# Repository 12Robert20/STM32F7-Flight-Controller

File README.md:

# 🚀 LayerByLayer Flight Controller v0.1.0

A high-performance, 4-layer custom Flight Controller designed in KiCad 8. Built around the powerful STM32F777 microcontroller, it features an advanced IMU, integrated OSD, and Blackbox logging capabilities, tailored for demanding FPV and autonomous flight applications.

---

## ✨ Key Features & Hardware Specifications

*   **Microcontroller:** `STM32F777VIT6` (ARM Cortex-M7, 216MHz, 2MB Flash, 512KB RAM)
*   **IMU (Gyro/Accel):** `LSM6DSV320XTR` (Connected via SPI6)
*   **OSD (On-Screen Display):** `MAX7456EUI+` (Analog Video Overlay, SPI4)
*   **Barometer:** `BMP280` (Altitude sensing, I2C1)
*   **Blackbox Flash:** `W25Q128JVS` (16MB/128Mbit SPI Flash for flight data logging, SPI3)
*   **USB Interface:** USB-C 2.0 with `USBLC6-2SC6` ESD protection diode.

---

## ⚡ Power Delivery Network (PDN)

To ensure clean video feeds and stable logic levels, the power delivery is split and filtered:
*   **Main 5V Buck Converter:** Direct LiPo input (VBAT) is stepped down by an `LMR51430Y` synchronous buck converter, providing a highly efficient 5V at up to 3A for the MCU, OSD, and external peripherals (VTX, Camera, GPS).
*   **Clean Video:** A dedicated LC filter is implemented before the VTX/Camera power rail to eliminate electrical noise generated by the ESCs and motors.
*   **3.3V Logic LDO:** An `AP2112K-3.3` linear regulator derives a clean 3.3V from the 5V rail to power the noise-sensitive STM32 MCU, IMU, Baro, and Flash memory.

---

## 🔌 Connectivity & Interfaces

| Interface | Bus / Pins | Description |
| :--- | :--- | :--- |
| **ESC / Motors** | `M1` - `M4` | 4x Motor Outputs (DShot600 compatible) |
| **Receiver (RX)** | `UART1` | CRSF Protocol (e.g., TBS Crossfire, ExpressLRS) |
| **GPS / Compass** | `UART2` + `I2C1` | GNSS Module connectivity |
| **Video TX (VTX)** | Video Out | 5V, GND, Video Signal (SpeedyBee TX800 VTX support) |
| **Camera** | Video In | 5V, GND, Video Signal (Analog Camera e.g., CADDXFPV) |
| **Debug** | `SWD` | SWCLK / SWDIO pads for ST-Link debugging |

---

## 🛠️ PCB Stackup (4-Layer)

To ensure signal integrity and controlled impedance for high-speed traces, a standard 4-layer stackup is utilized:
1.  **F.Cu (Top):** Signal & Components
2.  **In1.Cu (Inner 1):** Solid GND Plane
3.  **In2.Cu (Inner 2):** Split Power Planes (3.3V / 5V / VBAT)
4.  **B.Cu (Bottom):** Signal & Minor Components

---

## 🚧🚧🚧 📝 Firmware Compatibility (In Development) 🚧🚧🚧

This hardware is architected to be compatible with major open-source flight controller firmware. Custom target definition files are required to map the pins correctly.
*   **Betaflight** (Recommended for FPV)
*   **INAV** (Recommended for Autonomous Flight utilizing the onboard BMP280 and GNSS UART)

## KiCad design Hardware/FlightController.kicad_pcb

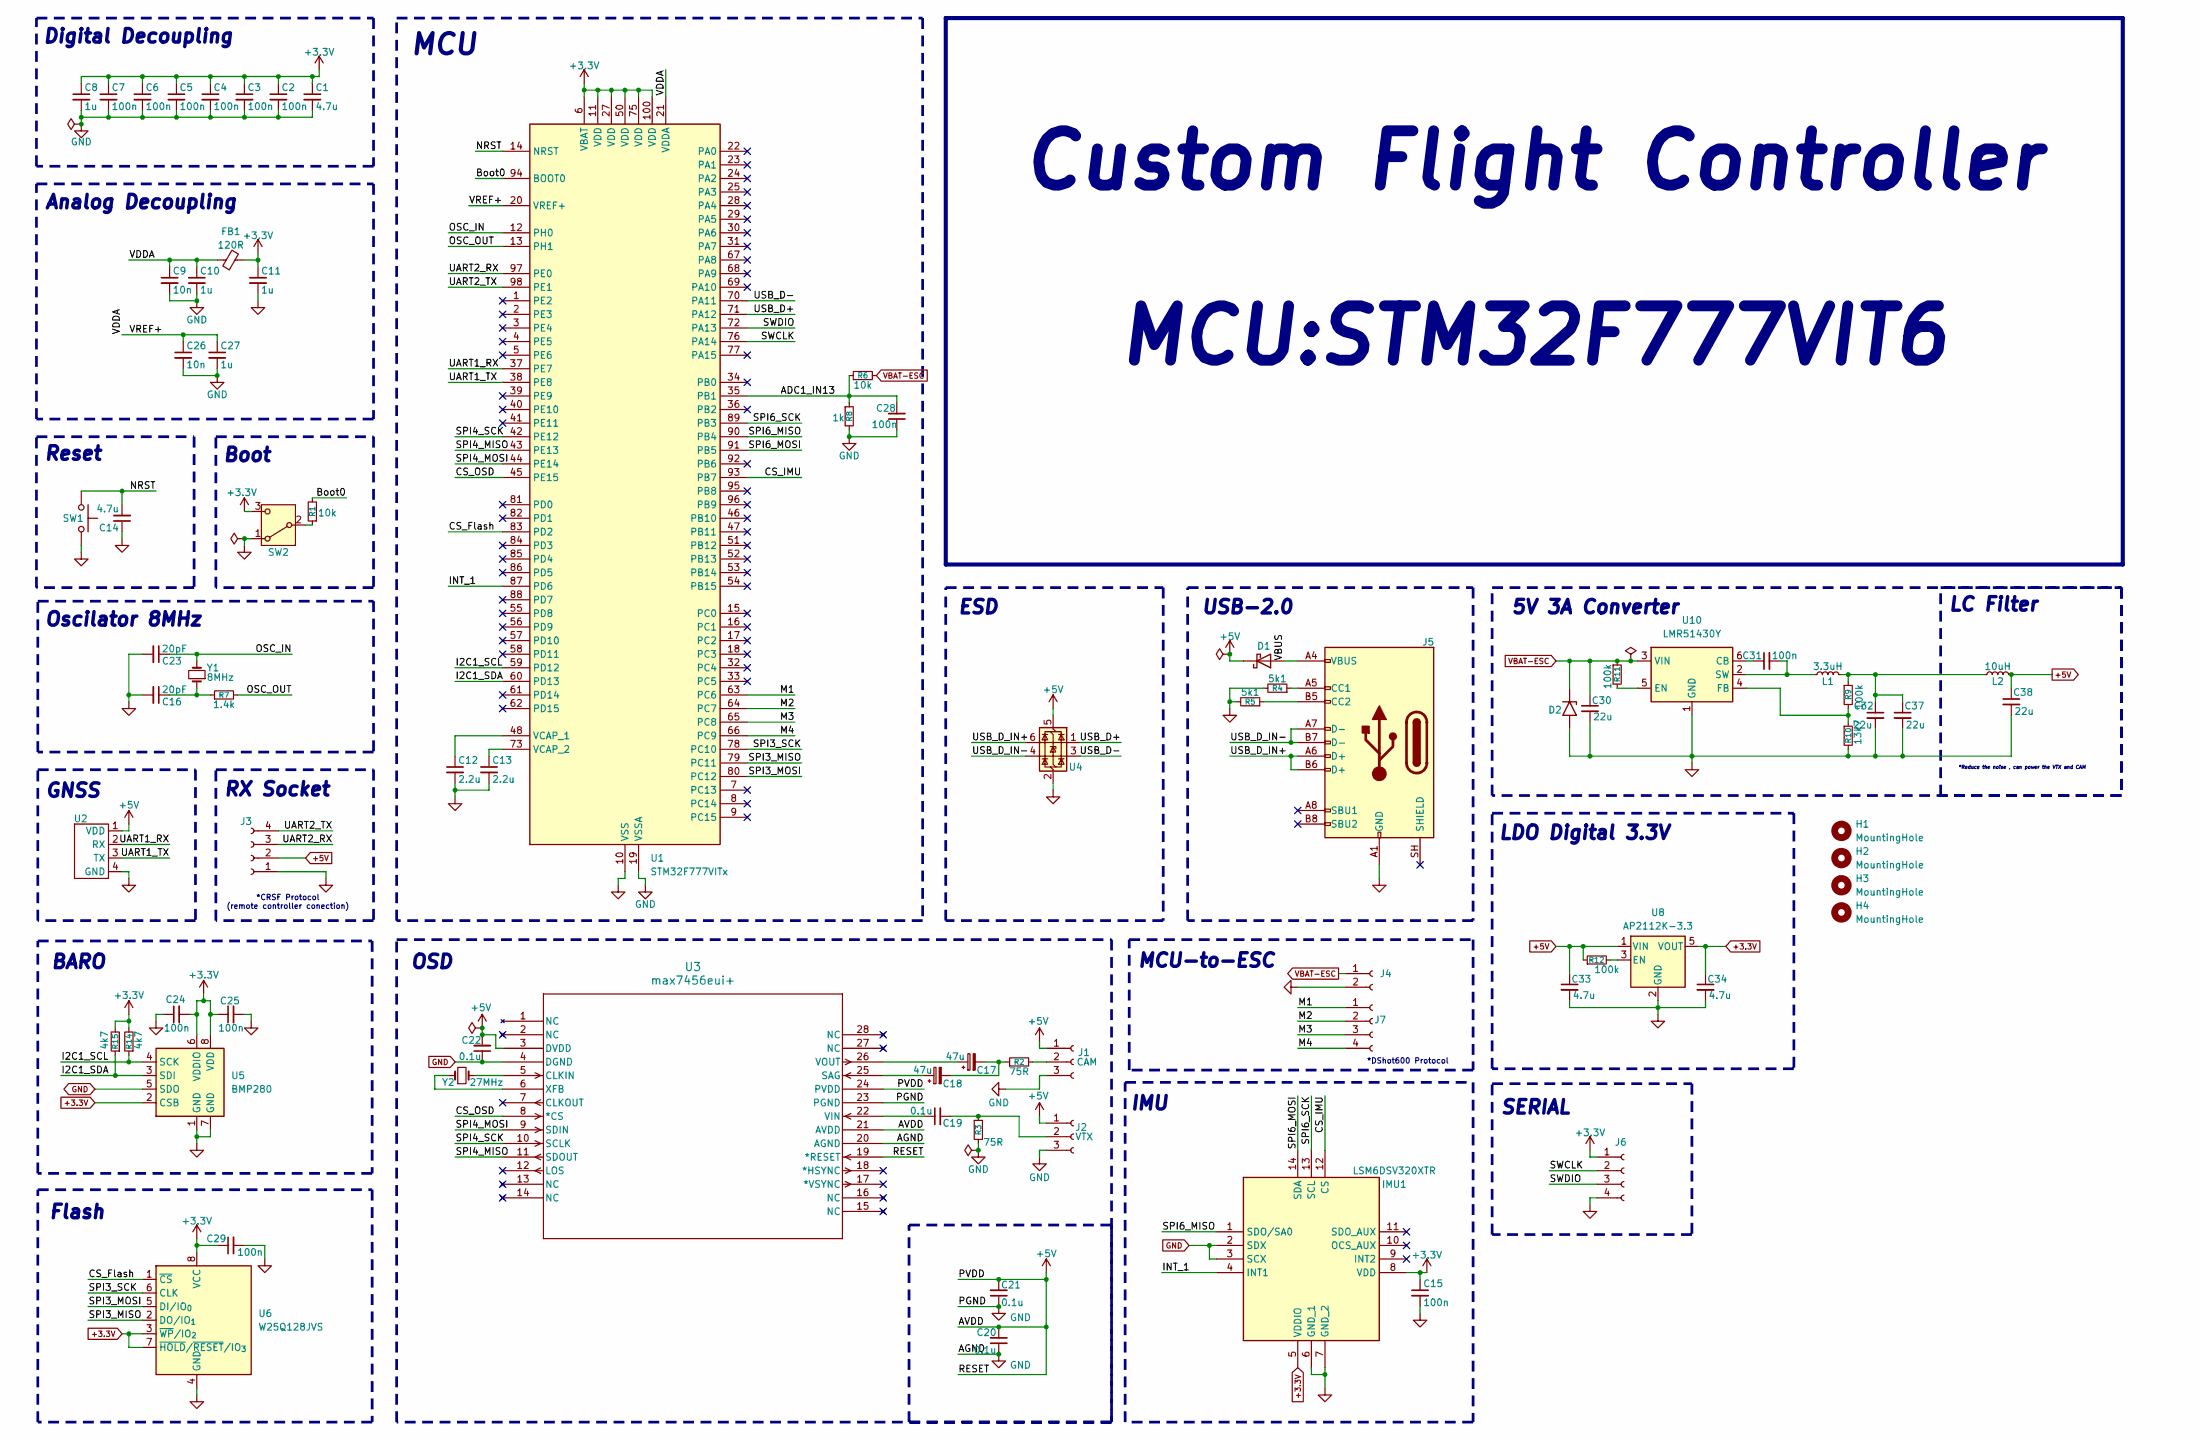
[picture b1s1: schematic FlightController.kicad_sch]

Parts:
C1, C14, C33, C34: 4.7u; C_0603_1608Metric
C2, C3, C4, C5, C6, C7, C15, C24, C25, C28, C29, C31: 100n; C_0402_1005Metric
C8, C10, C11, C27: 1u; C_0603_1608Metric
C9: 10n; C_0402_1005Metric
C12, C13: 2.2u; C_0603_1608Metric
C16, C23: 20pF; C_0402_1005Metric
C17, C18: 47u; C_0603_1608Metric
C19, C20, C21, C22: 0.1u; C_0402_1005Metric
C26: 10n; C_0603_1608Metric
C30, C32, C37, C38: 22u; C_1206_3216Metric
D1: D_Schottky; D_SMA
D2: SMAJ28A; D_SMA
FB1: 120R; L_0402_1005Metric
H1, H2, H3, H4: MountingHole; MountingHole_2.2mm_M2_DIN965_Pad
IMU1: LSM6DSV320XTR; LSM6DSV16BXTR; Manufacturer_Part_Number LSM6DSV320XTR; Mouser Part Number 511-LSM6DSV320XTR
J1: CAM; SolderingWirePad_1x03_SMD_2x4mm
J2: VTX; SolderingWirePad_1x03_SMD_2x4mm
J3: SolderingWirePad_1x04_SMD_2x4mm
J4: Conn_01x02_Socket; SolderWirePad_1x02_SMD_2x4mm
J5: USB_C_Receptacle_USB2.0_16P; USB_C_Receptacle_GCT_USB4105-xx-A_16P_TopMnt_Horizontal
J6, J7: Conn_01x04_Socket; SolderingWirePad_1x04_SMD_2x4mm
L1: 3.3uH; L_0402_1005Metric
L2: 10uH; L_0402_1005Metric
R1, R6: 10k; R_0402_1005Metric
R2, R3: 75R; R_0402_1005Metric
R4, R5: 5k1; R_0402_1005Metric
R7: 1.4k; R_0402_1005Metric
R8: 1k; R_0402_1005Metric
R9, R11, R12: 100k; R_0603_1608Metric
R10: 13k7; R_0402_1005Metric
R14, R15: 4k7; R_0402_1005Metric
SW1: SW_Omron_B3FS; SW_SPST_Omron_B3FS-100xP
SW2: SW_SPDT; SW_CK_JS202011AQN_DPDT_Angled
U1: STM32F777VITx; LQFP-100_14x14mm_P0.5mm
U2: GNSS; SolderingWirePad_1x04_SMD_2x4mm
U3: max7456eui+; 21-0108G_U28E-5_MXM-M
U4: USBLC6-2SC6; SOT-23-6_Handsoldering
U5: BMP280; Bosch_LGA-8_2x2.5mm_P0.65mm_ClockwisePinNumbering
U6: W25Q128JVS; SOIC-8_5.3x5.3mm_P1.27mm
U8: AP2112K-3.3; SOT-23-5
U10: LMR51430Y; SOT-23-6
Y1: 8MHz; Crystal_SMD_5032-2Pin_5.0x3.2mm
Y2: 27MHz; Crystal_SMD_5032-2Pin_5.0x3.2mm

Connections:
+3.3V: C1.1, C2.1, C3.1, C4.1, C5.1, C6.1, C7.1, C8.1, C11.1, C15.1, C24.2, C25.1, C29.1, C34.1, FB1.2, IMU1.5 (VDDIO), IMU1.8 (VDD), J6.1, R14.2, R15.2, SW2.3 (C), U1.6 (VBAT), U1.11 (VDD), U1.27 (VDD), U1.50 (VDD), U1.75 (VDD), U1.100 (VDD), U5.2 (CSB), U5.6 (VDDIO), U5.8 (VDD), U6.3 (~WP/IO_{2}), U6.7 (~HOLD/~RESET/IO_{3}), U6.8 (VCC), U8.5 (VOUT)
+5V: C20.2, C21.2, C22.2, C33.1, C38.1, D1.1 (K), J1.1, J2.1, J3.2, L2.2, R12.1, U2.1 (VDD), U3.3 (DVDD), U3.19 (*RESET), U3.21 (AVDD), U3.24 (PVDD), U4.5 (VBUS), U8.1 (VIN)
/ADC1_IN13: C28.2, R6.1, R8.1, U1.35 (PB1)
/Boot0: R1.2, U1.94 (BOOT0)
/CS_Flash: U1.83 (PD2), U6.1 (~CS)
/CS_IMU: IMU1.12 (CS), U1.93 (PB7)
/CS_OSD: U1.45 (PE15), U3.8 (*CS)
/I2C1_SCL: R14.1, U1.59 (PD12), U5.4 (SCK)
/I2C1_SDA: R15.1, U1.60 (PD13), U5.3 (SDI)
/INT_1: IMU1.4 (INT1), U1.87 (PD6)
/M1: J7.1, U1.63 (PC6)
/M2: J7.2, U1.64 (PC7)
/M3: J7.3, U1.65 (PC8)
/M4: J7.4, U1.66 (PC9)
/NRST: C14.2, SW1.1, U1.14 (NRST)
/OSC_IN: C23.1, U1.12 (PH0), Y1.2
/OSC_OUT: R7.2, U1.13 (PH1)
/SPI3_MISO: U1.79 (PC11), U6.2 (DO/IO_{1})
/SPI3_MOSI: U1.80 (PC12), U6.5 (DI/IO_{0})
/SPI3_SCK: U1.78 (PC10), U6.6 (CLK)
/SPI4_MISO: U1.43 (PE13), U3.11 (SDOUT)
/SPI4_MOSI: U1.44 (PE14), U3.9 (SDIN)
/SPI4_SCK: U1.42 (PE12), U3.10 (SCLK)
/SPI6_MISO: IMU1.1 (SDO/SA0), U1.90 (PB4)
/SPI6_MOSI: IMU1.14 (SDA), U1.91 (PB5)
/SPI6_SCK: IMU1.13 (SCL), U1.89 (PB3)
/SWCLK: J6.2, U1.76 (PA14)
/SWDIO: J6.3, U1.72 (PA13)
/UART1_RX: U1.37 (PE7), U2.2 (RX)
/UART1_TX: U1.38 (PE8), U2.3 (TX)
/UART2_RX: J3.3, U1.97 (PE0)
/UART2_TX: J3.4, U1.98 (PE1)
/USB_D+: U1.71 (PA12), U4.1 (I/O1)
/USB_D-: U1.70 (PA11), U4.3 (I/O2)
/USB_D_IN+: J5.A6 (D+), J5.B6 (D+), U4.6 (I/O1)
/USB_D_IN-: J5.A7 (D-), J5.B7 (D-), U4.4 (I/O2)
/VBUS: D1.2 (A), J5.A4 (VBUS), J5.A9 (VBUS), J5.B4 (VBUS), J5.B9 (VBUS)
/VDDA: C9.1, C10.1, C26.1, C27.1, FB1.1, U1.20 (VREF+), U1.21 (VDDA)
GND: C1.2, C2.2, C3.2, C4.2, C5.2, C6.2, C7.2, C8.2, C9.2, C10.2, C11.2, C12.2, C13.2, C14.1, C15.2, C16.2, C20.1, C21.1, C22.1, C23.2, C24.1, C25.2, C26.2, C27.2, C28.1, C29.2, C30.2, C32.2, C33.2, C34.2, C37.2, C38.2, D2.2 (A2), IMU1.2 (SDX), IMU1.3 (SCX), IMU1.6 (GND_1), IMU1.7 (GND_2), J1.3, J2.3, J3.1, J4.2, J5.A1 (GND), J5.A12 (GND), J5.B1 (GND), J5.B12 (GND), J6.4, R3.2, R4.2, R5.2, R8.2, R10.2, SW1.2, SW2.1 (A), U1.10 (VSS), U1.19 (VSSA), U1.26 (VSS), U1.49 (VSS), U1.74 (VSS), U1.99 (VSS), U2.4 (GND), U3.4 (DGND), U3.20 (AGND), U3.23 (PGND), U4.2 (GND), U5.1 (GND), U5.5 (SDO), U5.7 (GND), U6.4 (GND), U8.2 (GND), U10.1 (GND)
unnamed: C16.1, R7.1, Y1.1
unnamed: C17.2, C18.2, R2.1
unnamed: C32.1, C37.1, L1.2, L2.1, R9.1
unnamed: J1.2, R2.2
unnamed: C19.2, J2.2, R3.1
unnamed: J5.A5 (CC1), R4.1
unnamed: J5.B5 (CC2), R5.1
unnamed: R1.1, SW2.2 (B)
unnamed: C12.1, U1.48 (VCAP_1)
unnamed: C13.1, U1.73 (VCAP_2)
unnamed: U3.5 (CLKIN), Y2.2
unnamed: C18.1, U3.25 (SAG)
unnamed: C19.1, U3.22 (VIN)
unnamed: C17.1, U3.26 (VOUT)
unnamed: U3.6 (XFB), Y2.1
unnamed: R12.2, U8.3 (EN)
unnamed: C31.1, U10.6 (CB)
unnamed: R11.2, U10.5 (EN)
unnamed: R9.2, R10.1, U10.4 (FB)
unnamed: C31.2, L1.1, U10.2 (SW)
VBAT-ESC: C30.1, D2.1 (A1), J4.1, R6.2, R11.1, U10.3 (VIN)

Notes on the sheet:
IMU
Digital Decoupling
GNSS
*DShot600 Protocol
OSD
Flash
ESD
5V 3A Converter
*Reduce the noise , can power the VTX and CAM
LC Filter
Boot
BARO
Analog Decoupling
LDO Digital 3.3V
Oscilator 8MHz
RX Socket
Reset
MCU
SERIAL
*CRSF Protocol (remote controller conection)
MCU-to-ESC
USB-2.0
Custom Flight Controller MCU:STM32F777VIT6

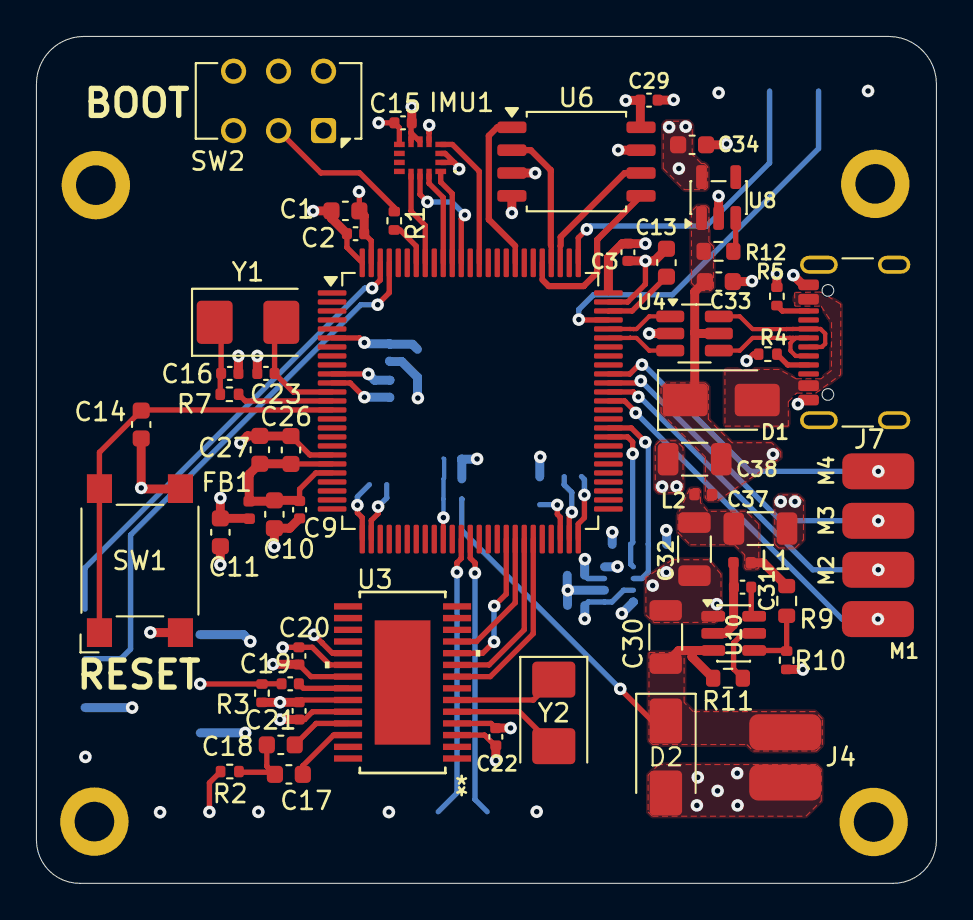
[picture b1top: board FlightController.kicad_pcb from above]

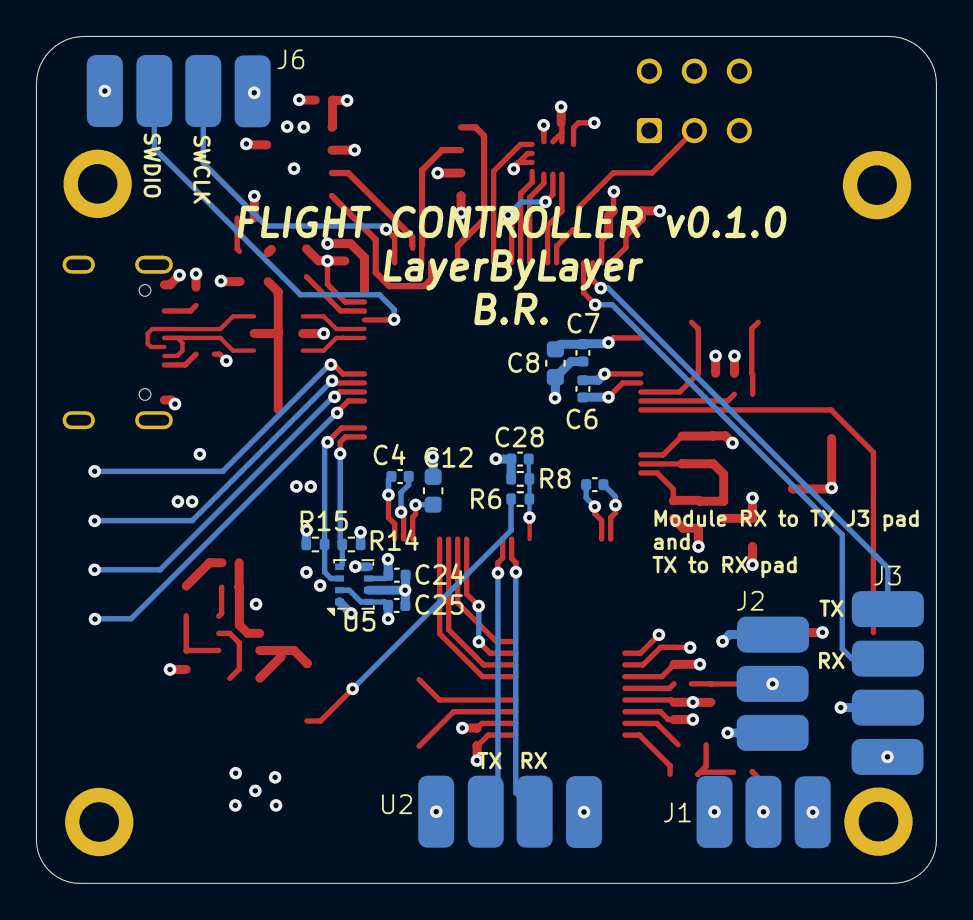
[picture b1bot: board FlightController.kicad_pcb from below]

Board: 4 copper layers, 50.0 x 47.0 mm, 79 parts (19 on the bottom side), 60 nets.
